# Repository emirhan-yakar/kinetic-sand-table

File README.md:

<div align="center">

### Kinetik Kum Sanatı Masası · Polar (θ-ρ) · Ø60 cm

Çelik bir bilyeyi kumun altından mıknatısla sürükleyerek sonsuz desen çizen,
**Türkiye'de üretilebilir**, açık tasarımlı premium kinetik sanat masası.

</div>

---

## Bu nedir?

DEVRAN, cam yüzeyin altında dönen bir kol (**θ** ekseni) ve kol üzerinde kayan bir taşıyıcının
(**ρ** ekseni) bir **N52 mıknatısı** taşıdığı, bu mıknatısın üstteki kumda bir **çelik bilyeyi**
sürükleyerek desen kazıdığı bir Sisyphus tipi kinetik masadır. Kenardaki **WS2812B LED halka**
ambiyans ışığı verir. Beyin bir **ESP32 + FluidNC**'dir; `.thr` (theta-rho) desenlerini oynatır.

Bu repo **fikirden satılabilir ürüne** giden tüm mühendislik + üretim dosyalarını içerir.

## Öne çıkanlar

- 🌀 Sonsuz, tekrarsız kinetik kum deseni (Atatürk imzası, spiral, özel)
- 🔇 Sessiz çalışma (TMC2209) · 💡 adreslenebilir LED ambiyans
- 📶 Wi-Fi / WebUI kontrol · SD desen kütüphanesi
- 🪵 Premium ceviz gövde + temperli cam · 🇹🇷 yerli üretilebilir
- 🔓 Açık kaynak yazılım (FluidNC + Dune Weaver)

## Üretim paketi

| Alan | Dosyalar |
|---|---|
| **Kontrol kartı** | KiCad Rev-B · Gerber · STEP · [JLCPCB paketi](hardware/pcb/jlcpcb/) (BOM+CPL) · [inceleme](docs/uretim/PCB_inceleme.md) |
| **Mekanizma** | [θ/ρ kinematik + kesit + hesap](docs/uretim/mekanizma_tasarim.md) |
| **Mekanik üretim** | [DXF + STEP](docs/uretim/dxf/) (şasi/ayak/kol) · [teknik çizim](docs/uretim/MONTAJ_CIZIM.pdf) · [montaj](docs/uretim/montaj.md) |
| **Elektrik** | [harness + pinout](docs/uretim/elektrik_montaj.md) · [talimat PDF](docs/uretim/ELEKTRIK_TALIMATI.pdf) · [QA/FCT](docs/uretim/QA_kontrol_listesi.md) |
| **Firmware** | [FluidNC config](firmware/fluidnc_config.yaml) · [mimari](firmware/README.md) |
| **İş** | [üretim dosyası (NPI)](docs/uretim/URETIM_DOSYASI.md) · [datasheet](docs/DEVRAN_datasheet.pdf) · [pitch](docs/DEVRAN_pitch.pdf) · [BOM/maliyet](docs/uretim/BOM_uretim.md) |
| **Görsel** | render + reklam videosu (`render/`) · interaktif 3D sim (`render/viewer.html`) |

> 🌐 **Web sitesi:** kök `index.html` (yerel: `python3 -m http.server`) — GitHub Pages açılırsa canlı.

## Durum (dürüst)

| Alt sistem | Durum |
|---|---|
| Mekanik tasarım | 🟡 Tasarlandı (kinematik + çizim + DXF/STEP) — fiziksel prototip yok |
| Kontrol kartı (PCB) | 🟠 Rev-B, DRC temiz — **fiziksel üretilmedi/test edilmedi** |
| Firmware | 🟠 Mimari + config hazır — cihazda doğrulanmadı |
| BOM / maliyet / görsel | 🟢 Hazır |

**Sıradaki:** Fusion'da COTS fit doğrulama → PCB sipariş → bring-up → kalibrasyon → EVT/DVT.

## Maliyet & fiyat

Seri COGS ≈ **7.800 TL** (~$230) → hedef **MSRP ≈ 21.900 TL** (~$650, ~%64 brüt marj).
Benzer ürün $699. Yazılım açık kaynak (0 TL). Detay: [BOM/maliyet](docs/uretim/BOM_uretim.md).

## Repo yapısı

```
hardware/pcb/   KiCad tasarım, Gerber, STEP, JLCPCB paketi (üretim scriptleri)
firmware/       FluidNC config + desen üreteçleri (.thr)
render/         Blender sahne (scene.py), render'lar, reklam videosu, 3D sim (viewer.html)
docs/uretim/    mekanizma, montaj, elektrik, QA, BOM, DXF+STEP, teknik çizim/PDF'ler
docs/           datasheet, pitch, gerçeklik yol haritası
*.html          web sitesi (build_site.py ile MD'den üretilen sayfalar dahil)
```

## Yeniden üretmek

```bash
# Site (MD -> HTML sayfalar)        : python3 build_site.py
# Render/video (Blender 4.5)        : Blender --background --python render/scene.py -- hero|video
# PCB (KiCad 9 + Freerouting)       : hardware/pcb/freeroute.sh
# DXF/STEP                          : python3 docs/uretim/dxf/make_dxf.py && make_step.py
# Datasheet/pitch                   : python3 docs/marka_pdf.py
```

## Lisans & katkı

Açık kaynak tasarım. Ticari üretim için: PCB **fiziksel doğrulama** + **CE/elektrik güvenlik**
belgesi gereklidir. Katkı/issue/PR memnuniyetle. Tüm değişiklikler: [CHANGELOG.md](CHANGELOG.md).

<div align="center"><sub>DEVRAN · kinetik kum sanatı masası · github.com/emirhan-yakar/kinetic-sand-table</sub></div>

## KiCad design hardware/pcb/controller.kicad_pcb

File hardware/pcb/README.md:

# Kontrol Kartı / PCB Spesifikasyonu

## Strateji
- **Prototip (1–10 adet):** Özel PCB tasarlama. Hazır **MKS DLC32** veya
  **BTT** ESP32 tabanlı kontrol kartı kullan — TMC2209 sürücü yuvaları,
  endstop ve LED çıkışı hazır. Riski sıfırlar, hızlı doğrulama sağlar.
- **Seri (50+ adet):** Maliyet ve montaj için aşağıdaki tek kartı KiCad'de
  tasarla, **JLCPCB / PCBWay** (Çin, ucuz, SMT montaj dahil) veya yurt içi PCB
  firmasında bastır.

## Özel PCB — blok şema
```
            +12V DC giriş (fiş + ters polarite koruma D1)
               │
        ┌──────┴───────┐
   12V →│ Buck 12V→5V   │→ +5V (ESP32, LED, lojik)
        └──────────────┘
               │5V                          │12V
        ┌──────┴───────┐            ┌────────┴─────────┐
        │   ESP32-WROOM │            │ TMC2209 #1 (θ)   │→ NEMA17 θ
        │   -32         │── UART ───▶│ TMC2209 #2 (ρ)   │→ slip ring → NEMA17 ρ
        │               │   STEP/DIR └──────────────────┘
        │   GPIO ───────┼─[330Ω]─▶ DIN  WS2812B LED halka
        │   3v3 lojik   │          (5V güç + 1000µF kondansatör)
        │   GPIO ◀──────┼── endstop (θ home opto/mikro switch)
        └───────────────┘
```

## Pin haritası (Dune Weaver firmware ile uyumlu — `firmware/` bkz.)
| İşlev | ESP32 GPIO | Not |
|---|---|---|
| θ STEP / DIR | 19 / 18 | TMC2209 #1 |
| ρ STEP / DIR | 21 / 5 | TMC2209 #2 (sinyaller slip ring'den) |
| TMC UART (her ikisi) | 17 (TX)/16 (RX) | tek hat, adresli |
| EN (ortak) | 25 | sürücü enable |
| θ endstop / home | 22 | opto veya mikro switch |
| WS2812B DIN | 4 | seri direnç 330Ω |
| Buck enable / fan | 23 | opsiyonel |

## KiCad bileşen listesi (özel PCB)
- ESP32-WROOM-32E modülü (veya ESP32-DevKit header)
- 2× TMC2209 step sürücü (modül soketi veya SMD)
- MP1584 / LM2596 buck (12V→5V, ≥3A) — LED akımı için 5V hattını boyutlandır
- Giriş: DC jack/klemens, P-MOSFET ters polarite koruma, TVS diyot
- WS2812 hattı: 330Ω seri direnç + 1000µF/16V elektrolitik kondansatör
- Endstop konnektörü, motor için 4'lü JST/klemens (×2), slip ring klemensi
- Decoupling: 100nF × bolca, ESP32 EN/BOOT için RC + butonlar (programlama)

## Slip ring notu (KRİTİK — yuvarlak masaya özel)
Kol sürekli döndüğü için **ρ motorunun 4 bobin kablosu** dönen koldan sabit
karta **slip ring** üzerinden gelir. En az **6 kanallı** kapsül slip ring seç
(4 motor + 2 yedek/LED). Sinyal yerine motor bobinlerini geçirmek en basitidir
(ρ sürücüsü sabit kartta kalır). Slip ring kontak direnci düşük olmalı; ρ
akımını TMC2209'da makul (~0.6–0.9A) tut.

---

# ÜRETİLEN DOSYALAR

Kart, KiCad olmadan saf Python (`gerbonara`) ile **kod olarak** tasarlandı.
Yeniden üretmek için:
```
pip install --user gerbonara
python3 pcb_gen.py
```

## Dosya manifestosu
| Yol | İçerik |
|---|---|
| `pcb_gen.py` | Kartı üreten script (yerleşim + yönlendirme + GND plane + render) |
| `board3d.scad` | Kartın **3D dizgi modeli** (OpenSCAD → STL) |
| `controller.net` | KiCad'e aktarılabilir **netlist** (26 net) |
| `gerbers/*.gtl .gbl .gts .gbs .gto .gbo .gko` | Gerber katmanları (RS-274X) |
| `gerbers/controller-PTH.drl` / `-NPTH.drl` | Excellon delik dosyaları |
| `plots/*.svg` (+ `.png`) | Her katmanın çizimi + üst/alt kompozit + **assembly drawing** |

## Katman dizilimi (stackup) — 2 katman, 1.6mm FR4
| Gerber | KiCad adı | İçerik |
|---|---|---|
| `.gtl` | F.Cu | üst bakır: sinyal + güç izleri, padler |
| `.gbl` | B.Cu | **GND ground plane** (clearance'lı dolgu) |
| `.gts`/`.gbs` | F/B.Mask | lehim maskesi açıklıkları |
| `.gto`/`.gbo` | F/B.Silkscreen | bileşen konturları, pin-1, ratsnest kılavuzu |
| `.gko` | Edge.Cuts | kart sınırı 100×75mm + 4× Ø3.2 montaj deliği |

## Katman çizimleri (plots/)
- `composite-top.svg` / `composite-bottom.svg` — üst/alt birleşik görünüm
- `top_cu.svg`, `bot_cu.svg` (GND plane), `*_mask`, `*_silk`, `edge`
- `assembly.svg` — etiketli yerleşim/dizgi çizimi (montaj için)

## Yönlendirme durumu
- GND tamamen **alt katman ground plane** ile çözüldü (router'a girmez).
- Sinyal + güç: **26/32 segment** otomatik yönlendirildi (çakışma kontrollü).
- Kalan **6 segment** üst silk'te **kesik çizgi (ratsnest)** olarak işaretli —
  yoğun ESP32 çevresi sinyalleri. Bunlar KiCad'de elle/autorouter ile tamamlanır.

## ⚠️ Üretim öncesi (ZORUNLU)
Bu Gerber'lar geometrik olarak geçerlidir ve fabrikaya yüklenebilir, ancak
**seri üretimden önce KiCad'de DRC** (tasarım kuralı kontrolü) çalıştırılmalı:
1. KiCad → yeni PCB → `controller.net` ile **"Update PCB from netlist"**.
2. `gerbers/` Gerber'larını referans alarak yerleşimi içe aktar veya yeniden yerleştir.
3. 6 ratsnest segmentini tamamla, **DRC** çalıştır (clearance, annular ring).
4. `kicad-cli pcb export gerbers` ile doğrulanmış final Gerber + `step` 3D üret.

## Fabrikaya gönderim (JLCPCB / PCBWay)
- `gerbers/` klasörünü zip'le → yükle. 2 katman, 1.6mm, HASL, 5/5 mil rahat.
- Delikler: PTH (`-PTH.drl`) + NPTH (`-NPTH.drl`, montaj delikleri).
- Adetli dizgi (SMT) istiyorsan: özel PCB'yi SMD bileşenlerle tasarlayıp
  BOM + CPL ekle. Prototipte modüller (ESP32/TMC/buck) header'a takılır → elde lehim.

## Kart üzeri bileşenler (BOM özeti)
| Ref | Bileşen | Not |
|---|---|---|
| U1 | ESP32-DevKitC (2×15) | beyin |
| A1/A2 | TMC2209 StepStick | θ / ρ sürücü |
| BK1 | MP1584 buck | 12V→5V |
| J1 | 2p klemens | 12V giriş |
| J2/J3 | 4p klemens | θ / ρ motor (J3 slip ring'e) |
| J4 | 3p klemens | WS2812B LED (5V/DIN/GND) |
| J5 | 3p klemens | endstop (3V3/SIG/GND) |
| R1 | 330Ω 0805 | LED DIN seri direnç |
| C1 | 1000µF | 5V tampon |
| C2/C3 | 100nF 0805 | sürücü decoupling |

---

# KİCAD İLE FİNAL ÇIKTI (Gerber + STEP 3D)

Kart artık gerçek bir **KiCad 9 projesi** olarak da üretiliyor — gerçek footprint'ler,
net'ler, GND ground plane ve KiCad'in kendi motoruyla export edilmiş Gerber + STEP.

## Araç zinciri
```
python build_kicad.py   # pcbnew API ile controller.kicad_pcb uretir
bash   kicad_export.sh   # kicad-cli ile final/ -> Gerber + STEP + PDF + DRC
```
> KiCad ~/Applications/KiCad.app altında (9.0.9). `build_kicad.py` KiCad'in
> kendi python'u ile çalışır (bkz. script başı / kicad_export.sh içindeki yol tespiti).

## Üretilen dosyalar
| Yol | İçerik |
|---|---|
| `controller.kicad_pcb` | KiCad PCB (GUI'de açılır) — yerleşim + 25 net + GND zone |
| `build_kicad.py` | pcbnew ile kartı kuran script (footprint + net + iz + zone) |
| `kicad_export.sh` | kicad-cli export (Gerber/Drill/STEP/PDF/DRC) |
| `final/gerbers/*.gbr` + `controller.drl` | **KiCad'in ürettiği final Gerber + Excellon** |
| `final/controller.step` | **STEP 3D model** (2.1 MB, ISO-10303, e-CAD/mekanik için) |
| `final/top.pdf` / `bottom.pdf` | katman PDF çıktıları |
| `final/drc.json` + `DRC_SUMMARY.txt` | DRC raporu |
| `final/plots/final-B_Cu-groundplane.png` | alt katman GND plane render'ı |

## Durum — Freerouting ile TAM ROUTING ✅
- ✅ **Tüm sinyaller routlu** — DRC **ratsnest = 0** (Freerouting 23 sinyal netini
  tamamladı: 139 iz segmenti + 3 via).
- ✅ **Bakır kısa devre yok** (DRC `shorting_items = 0`).
- ✅ **Bakır clearance ihlali yok** (zone clearance kuralı self-fill geometrisine
  göre ayarlandı).
- ✅ **GND ground plane** alt katmanda dolu (clearance'lı), Gerber'da mevcut.
- ✅ **STEP 3D** geçerli (jenerik MaiXu klemens STEP modeli kütüphanede yok, atlandı).
- ⚠️ Kalan **148 DRC ihlali kozmetik**: 129'u `silk_*` (KiCad kütüphane
  footprint'lerinin kendi silkscreen'i pad/birbirine biniyor — fabrikalar kabul eder),
  geri kalan ~12'si self-fill plane artefaktı (`isolated_copper`, `starved_thermal`).
  **KiCad GUI'de `B` (Fill All Zones)** ile yeniden doldurunca bunlar da temizlenir.

## Freerouting akışı (otomatik routing)
`pcbnew` DSN export'u headless'ta çalışmadığı için DSN'i geometriden ürettik,
SES'i kendimiz ayrıştırdık. Java 25 + Freerouting 2.2.4 gerekir.
```
JAVA=~/jdk25/.../java FREEROUTING_JAR=/path/freerouting.jar bash freeroute.sh
```
| Script | İş |
|---|---|
| `make_dsn.py` | `controller.kicad_pcb` → Specctra **`controller.dsn`** (GND = B.Cu plane) |
| (Freerouting) | `controller.dsn` → **`controller.ses`** (headless autoroute) |
| `build_kicad.py` (`SES_FILE=...`) | SES route'larını fresh board'a uygula + GND plane yeniden doldur |
| `freeroute.sh` | yukarıdakileri zincirler + `kicad_export.sh` |

## Üretim öncesi son adım (KiCad GUI'de)
1. `controller.kicad_pcb`'yi aç → **`B`** ile zone'ları yeniden doldur (kozmetik DRC temizliği).
2. İstersen silkscreen referans metinlerini görünür yap / yeniden konumla.
3. **DRC** → `kicad_export.sh` ile final Gerber/STEP'i tazele.

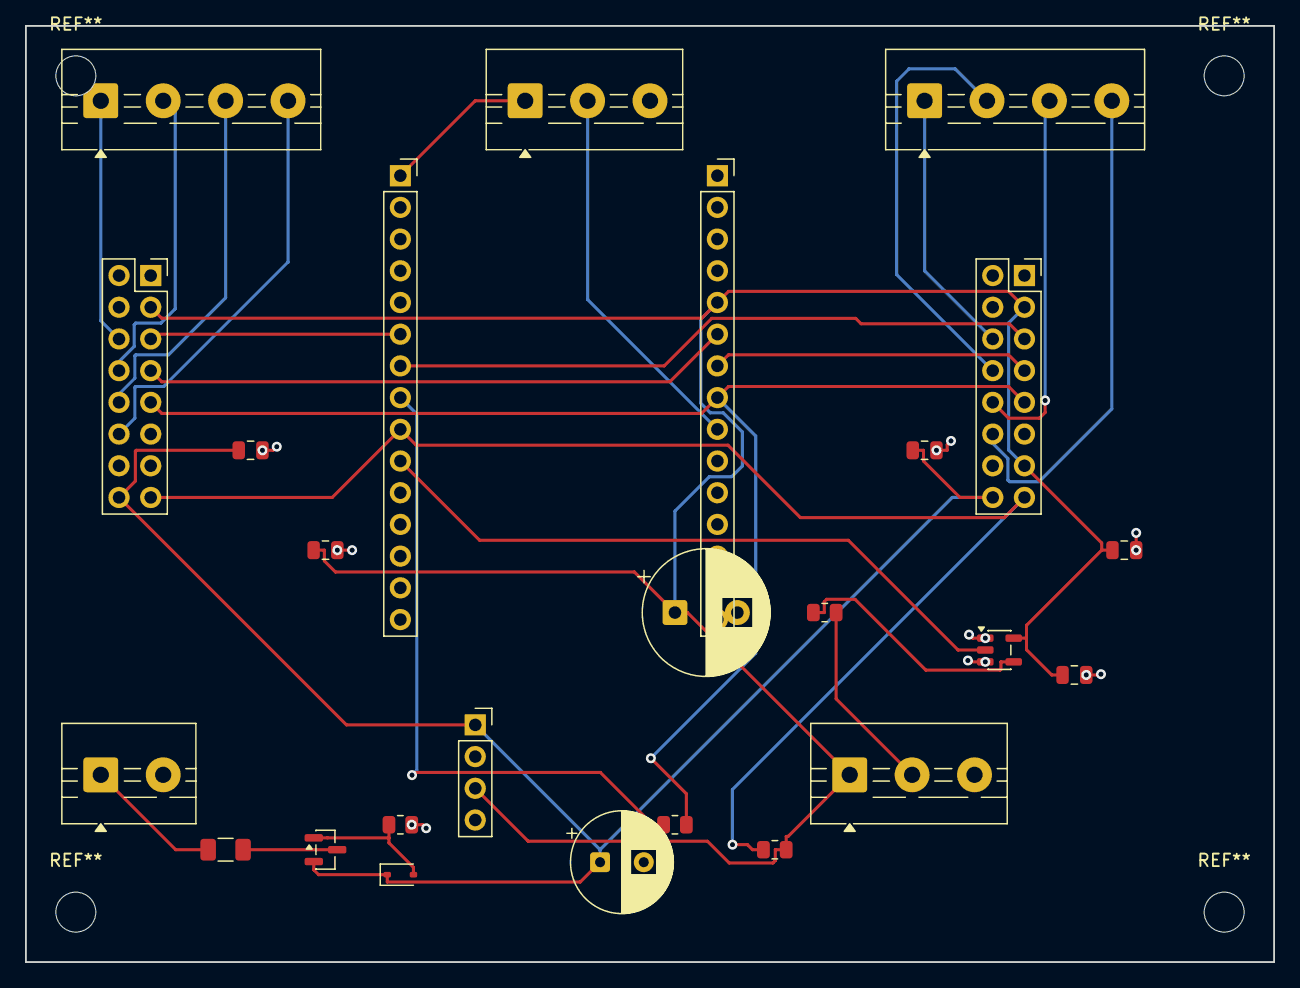
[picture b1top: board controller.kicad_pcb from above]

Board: 2 copper layers, 100.0 x 75.0 mm, 25 parts (0 on the bottom side), 26 nets.

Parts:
A1, A2: PinSocket_2x08_P2.54mm_Vertical
BK1: PinSocket_1x04_P2.54mm_Vertical
C1: CP_Radial_D10.0mm_P5.00mm
C2, C3, C5, C7, C8: C_0805_2012Metric
C6: CP_Radial_D8.0mm_P3.50mm
D1: D_SOD-323
F1: Fuse_1206_3216Metric
J1: TerminalBlock_MaiXu_MX126-5.0-02P_1x02_P5.00mm
J2, J3: TerminalBlock_MaiXu_MX126-5.0-04P_1x04_P5.00mm
J4, J5: TerminalBlock_MaiXu_MX126-5.0-03P_1x03_P5.00mm
Q1: SOT-23
R1, R2, R3, R4: R_0805_2012Metric
U1L, U1R: PinSocket_1x15_P2.54mm_Vertical
U2: SOT-23-5

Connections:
N_3V3: J5.1, U1L.1
N_5V: A1.3, A2.3, A2.13, BK1.3, C1.1, C2.1, C3.1, C5.1, J4.1, R3.2, U1R.5, U2.5
N_12V: A1.16, A2.16, BK1.1, C6.1, C7.1, C8.1, D1.1, Q1.2
N_12VF: F1.2, Q1.3
N_12VIN: F1.1, J1.1
N_EN: A1.15, A2.15, R3.1, U1L.9
N_ENDSTOP: J5.2, U1R.9
N_GND: A1.1, A1.2, A1.4, A1.11, A1.13, A1.14, A2.1, A2.2, A2.4, A2.11, A2.14, BK1.2, BK1.4, C1.2, C2.2, C3.2, C5.2, C6.2, C7.2, C8.2, J1.2, J4.3, J5.3, R2.2, U1R.1, U1R.15, U2.1, U2.3
N_LEDDIN: J4.2, R1.2
N_LEDDIN5: R1.1, U2.4
N_LEDG: U1L.10, U2.2
N_PDN: A1.9, A2.9, R4.2, U1R.8
N_PGATE: D1.2, Q1.1, R2.1
N_RHDIR: A2.5, U1L.7
N_RHSTEP: A2.7, U1R.7
N_THDIR: A1.5, U1L.6
N_THSTEP: A1.7, U1R.6
N_UART_TX: R4.1, U1L.8
RHM_A1: A2.6, J3.1
RHM_A2: A2.8, J3.2
RHM_B1: A2.10, J3.3
RHM_B2: A2.12, J3.4
THM_A1: A1.6, J2.1
THM_A2: A1.8, J2.2
THM_B1: A1.10, J2.3
THM_B2: A1.12, J2.4

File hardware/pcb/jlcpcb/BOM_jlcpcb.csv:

Comment,Designator,Footprint,LCSC Part #
330,R1,0805,C17630
100k,R2,0805,C17407
10k,R3,0805,C17414
1k,R4,0805,C17513
100nF,"C2,C3,C5,C7,C8",0805,C49678
74AHCT1G125,U2,SOT-23-5,DOGRULA
AO3401A,Q1,SOT-23,C15127
BZT52C10 10V,D1,SOD-323,DOGRULA
PTC 3A,F1,1206,DOGRULA

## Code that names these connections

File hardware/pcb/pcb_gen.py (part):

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    # sol kolon (c=0)            sag kolon (c=1)
    (0,0):"N_3V3",  (1,0):"N_GND",
    (0,1):"N_EN_BTN",(1,1):"GPIO23",
    (0,5):"N_THDIR",(1,5):"N_THSTEP",   # gpio18 / gpio19
    (0,6):"N_RHDIR",(1,6):"N_RHSTEP",   # gpio5  / gpio21
    (0,7):"N_UART", (1,7):"N_UART_RX",  # gpio17 / gpio16
    (0,8):"N_EN",   (1,8):"N_ENDSTOP",  # gpio25 / gpio22
    (0,9):"N_LEDG", (1,4):"N_5V",       # gpio4  ; 5V pin
    (1,14):"N_GND",
}
header(ESP_X, ESP_Y, 2, 15, P, 25.4, esp_nets, "U1 ESP32",
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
